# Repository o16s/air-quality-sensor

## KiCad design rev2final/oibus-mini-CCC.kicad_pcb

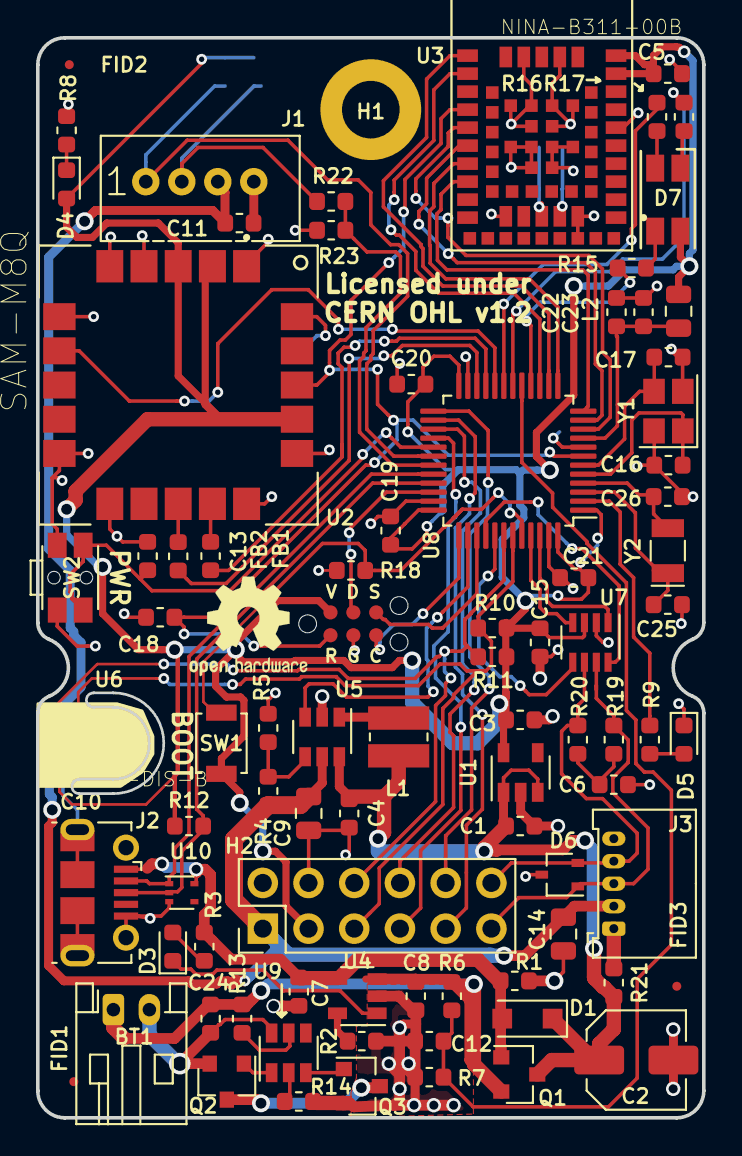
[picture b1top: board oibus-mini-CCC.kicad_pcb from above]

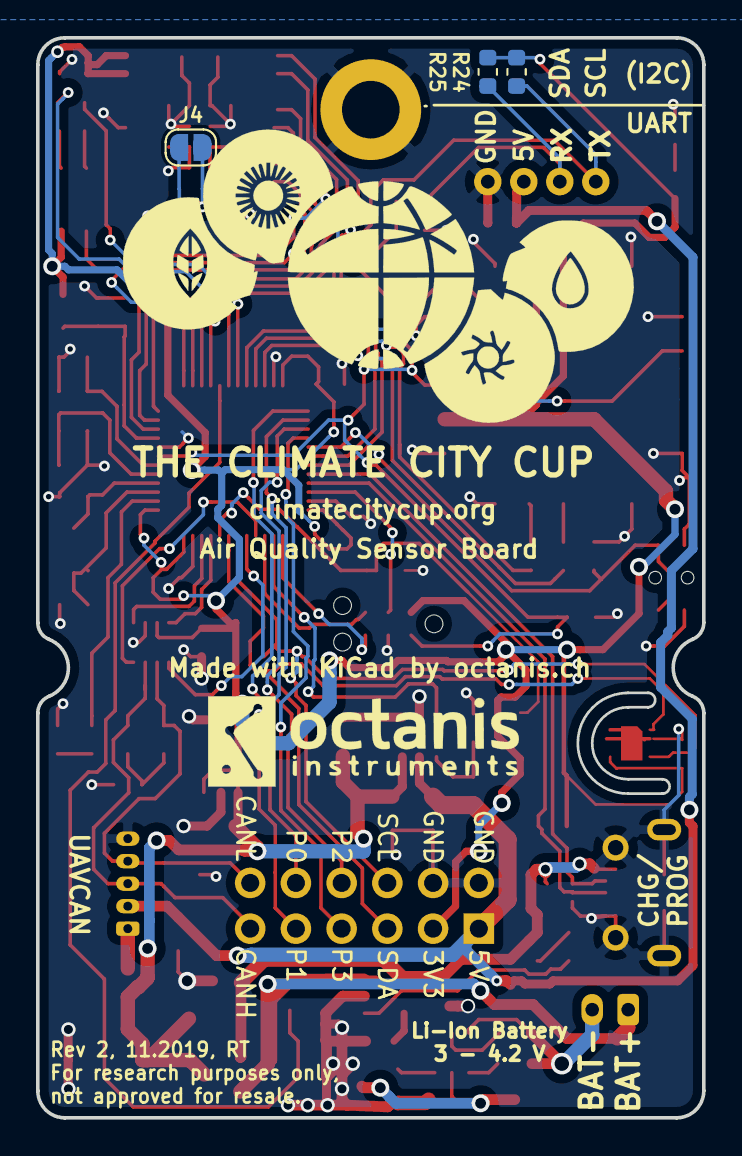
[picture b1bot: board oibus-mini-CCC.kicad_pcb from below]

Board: 2 copper layers, 37.0 x 60.0 mm, 90 parts (4 on the bottom side), 71 nets.

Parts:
B1: OI_Logo; octanis_instruments_logo
BT1: Battery_Cell; JST_PH_S2B-PH-K_1x02_P2.00mm_Horizontal
C1, C3, C22, C24: 1u; C_0603_1608Metric
C2: 47u 16V; C_Elec_5x5.4
C4, C7, C8: 4u7; C_0603_1608Metric
C5, C6, C10, C11, C13, C15, C18, C19, C20, C21: 100n; C_0603_1608Metric
C9, C14: 10u; C_0805_2012Metric
C12, C23: 10n; C_0603_1608Metric
C16, C17: 12p; C_0603_1608Metric
C25, C26: 10p; C_0603_1608Metric
D1: MBR120; D_SOD-123F
D3: LED_red; LED_0603_1608Metric
D4: LED_green; LED_0603_1608Metric
D5: LED_blue_side; LED_0603_1608Metric
D6: DNP; SOT-323_SC-70
D7: LED_RGBA; LED_RGB_1210
FB1, FB2: Ferrite_Bead; L_0603_1608Metric
FID1, FID2, FID3: Fiducial; Fiducial_0.5mm_Mask1mm
H1: MountingHole_Pad; MountingHole_3.2mm_M3_DIN965_Pad
H2: DNP; OIBUS12_connector
J1: Conn_01x04_Female; Grove_1x04
J2: USB_B_Micro; USB_Micro-B_Molex-105017-0001
J3: DNP; Molex_PicoBlade_53048-0510_1x05_P1.25mm_Horizontal
J4: Conn_01x02_Female; SolderJumper-2_P1.3mm_Open_RoundedPad1.0x1.5mm
L1: 4u7; L_Wuerth_MAPI-3010
L2: 10uH; L_0805_2012Metric
P1: TC2030-MCP; TC2030-MCP-NL
Q1: DMG3415U-7; SOT-23
Q2, Q3: NMOS; SOT-23
R1, R5, R6: 309k; R_0603_1608Metric
R2: 5.1k; R_0603_1608Metric
R3, R14, R15, R16: 1.2k; R_0603_1608Metric
R4, R7: 976k; R_0603_1608Metric
R8, R19, R20, R21, R23, R24, R25: DNP; R_0603_1608Metric
R9, R13: 430R; R_0603_1608Metric
R10, R11, R12, R18: 4.7k; R_0603_1608Metric
R17: 2.7k; R_0603_1608Metric
R22: 0R; R_0603_1608Metric
SW1: SW_Push; SW_SPST_B3U-1000P
SW2: SW_Push; SW_SPST_EVQP7C
U1: AP2112K-3.3; SOT-23-5
U2: SAM-M8Q; XCVR_SAM-M8Q
U3: NINA-B311-00B; XCVR_NINA-B312-00B
U4: MCP73831-2-OT; SOT-23-5
U5: MCP1624T; SOT-23-6
U6: SHT31-DIS-B; SON50P250X250X100-9N
U7: DNP; SOT-23-8
U8: STM32F303CCTx; LQFP-48_7x7mm_P0.5mm
U9: DW01C-G; SOT-23-6
U10: TPD3E001DRLR; SOT-553
Y1: 16M; Crystal_SMD_SeikoEpson_FA238-4Pin_3.2x2.5mm
Y2: 32kHz; Crystal_SMD_MicroCrystal_CC7V-T1A-2Pin_3.2x1.5mm

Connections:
+3V3: C3.2, C5.2, C10.2, C15.2, C19.2, C20.2, C21.2, D4.2, D7.4, H2.3, L2.1, P1.2, R10.1, R11.1, R12.1, R24.1, R25.1, SW1.2, U1.5, U2.2, U2.3, U2.17, U3.9, U3.10, U6.5, U7.3, U8.1, U8.24, U8.36, U8.48
+5V: C9.2, C11.2, C14.2, H2.1, J1.3, J3.2, R4.1, U5.5
+BATT: BT1.1, C8.2, C24.2, Q1.2, R6.1, R13.1, U4.3
/5V_EN: U5.3, U8.38
/BAT_MEAS: C12.2, R6.2, R7.1, U8.17
/BLUE: R15.1, U8.16
/BOOT: R18.1, SW1.1, U8.44
/CAN_H: D6.1, H2.11, J3.3, R19.1, U7.7
/CAN_L: D6.2, H2.12, J3.4, R20.2, U7.6
/CAN_LED: R9.1, U8.2
/CAN_RX: U7.4, U8.45
/CAN_SHDN: U7.5, U8.41
/CAN_SILENT: U7.8, U8.40
/CAN_TX: U7.1, U8.46
/GPS_TIME: U2.7, U8.20
/GREEN: R16.1, U8.19
/RED: R17.1, U8.18
/SCL: H2.6, R11.2, U6.4, U8.42
/SDA: H2.5, R10.2, U6.1, U8.43
/SPI_MISO: H2.8, U8.27
/SPI_MOSI: H2.7, U8.28
/SPI_SCK: H2.9, U8.26
/SPS_TX_EXT: J1.2, R22.1, R25.2
/SWDCLK: P1.5, U8.37
/SWDIO: P1.4, U8.34
/SWDSWO: P1.6, U8.39
/USB_DM: J2.2, U8.32, U10.1
/USB_DP: J2.3, R12.2, U8.33, U10.2
/VIN: C1.2, C2.1, C4.2, D1.1, L1.1, Q1.3, R21.2, U1.1, U1.3, U5.6
/on_off: C13.1, SW2.1, U8.29
/~RESET: C18.1, P1.1, U2.18, U3.19, U8.7
/~SPI_ADS_CS: H2.10, U8.25
GND: C1.1, C2.2, C3.1, C4.1, C5.1, C6.1, C7.2, C8.1, C9.1, C10.1, C11.1, C12.1, C13.2, C14.1, C15.1, C16.2, C17.1, C18.2, C19.1, C20.1, C21.1, C22.1, C23.1, C25.2, C26.1, D5.1, D6.3, H1.1, H2.2, H2.4, J1.4, J2.5, J2.6, J3.5, P1.3, Q3.2, R1.2, R2.2, R5.2, R7.2, R8.2, R14.2, R18.2, R23.2, SW2.2, U1.2, U2.1, U2.4, U2.5, U2.6, U2.10, U2.11, U2.15, U2.16, U2.20, U3.6, U3.12, U3.14, U3.26, U3.30, U3.53, U3.EGP1, U3.EGP2, U3.EGP3, U3.EGP4, U3.EGP5, U3.EGP6, U3.EGP7, U3.EGP8, U3.EGP9, U3.EGP10, U3.EGP11, U3.EGP12, U4.2, U5.2, U6.2, U6.7, U6.8, U6.9, U7.2, U8.8, U8.23, U8.35, U8.47, U10.3, Y1.2, Y1.4
GPS_RX: FB1.1, U8.21
GPS_TX: FB2.1, U8.22
NINA_CTS: U3.21, U8.11
NINA_DSR: U3.17, U8.15
NINA_DTR: U3.16, U8.14
NINA_RTS: U3.20, U8.10
NINA_RX: U3.23, U8.12
NINA_TX: U3.22, U8.13
unnamed: BT1.2, C24.1, Q2.2, U9.6
unnamed: C6.2, R19.2, R20.1
unnamed: C16.1, U8.5, Y1.1
unnamed: C17.2, U8.6, Y1.3
unnamed: C22.2, C23.2, L2.2, U8.9
unnamed: C25.1, U8.3, Y2.1
unnamed: C26.2, U8.4, Y2.2
unnamed: D3.1, U4.1
unnamed: D3.2, R3.2
unnamed: D4.1, R8.1
unnamed: D5.2, R9.2
unnamed: D7.1, R17.2
unnamed: D7.2, R16.2
unnamed: D7.3, R15.2
unnamed: FB1.2, U2.14
unnamed: FB2.2, U2.13
unnamed: J3.1, R21.1
unnamed: J4.1, U3.29
unnamed: J4.2, U3.28
unnamed: L1.2, U5.1
unnamed: Q2.1, U9.1
unnamed: Q2.3, Q3.3
unnamed: Q3.1, U9.3
unnamed: R2.1, U4.5
unnamed: R4.2, R5.1, U5.4
unnamed: R13.2, U9.5
unnamed: R14.1, U9.2
SPS_RX: J1.1, R24.2, U8.30
SPS_TX: R22.2, R23.1, U8.31
VBUS: C7.1, D1.2, J2.1, Q1.1, R1.1, R3.1, U4.4, U10.5

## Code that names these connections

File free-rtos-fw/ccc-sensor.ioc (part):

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Mcu.Name=STM32F303C(B-C)Tx
Mcu.Package=LQFP48
Mcu.UserName=STM32F303CCTx
PA0.Mode=CTS_RTS
PA0.Signal=USART2_CTS
PA1.Mode=CTS_RTS
PA1.Signal=USART2_RTS
PA10.Mode=Asynchronous
PA10.Signal=USART1_RX
PA11.Mode=Device
PA11.Signal=USB_DM
PA12.Mode=Device
PA12.Signal=USB_DP
PA13.Mode=Serial_Wire
PA13.Signal=SYS_JTMS-SWDIO
PA14.Mode=Serial_Wire
PA14.Signal=SYS_JTCK-SWCLK
PA15.GPIOParameters=PinState,GPIO_Label
PA15.GPIO_Label=LDO_5V_EN
PA15.PinState=GPIO_PIN_SET
PA15.Signal=GPIO_Output
PA2.Mode=Asynchronous
PA2.Signal=USART2_TX
PA3.Mode=Asynchronous
PA3.Signal=USART2_RX
PA4.GPIOParameters=GPIO_Label
PA4.GPIO_Label=NINA_DTR
PA4.Signal=GPIO_Input
PA5.GPIOParameters=GPIO_Label
PA5.GPIO_Label=NINA_DSR
PA5.Signal=GPIO_Output
PA7.Mode=IN4-Single-Ended
PA7.Signal=ADC2_IN4
PA9.Mode=Asynchronous
PA9.Signal=USART1_TX
PB0.GPIOParameters=GPIO_Label
PB0.GPIO_Label=CAN_SILENT
PB0.Signal=GPIO_Output
PB1.GPIOParameters=GPIO_Label
PB1.GPIO_Label=CAN_SHDN
PB1.Signal=GPIO_Output
PB10.Mode=Asynchronous
PB10.Signal=USART3_TX
PB11.Mode=Asynchronous
PB11.Signal=USART3_RX
PB12.GPIOParameters=GPIO_Label
PB12.GPIO_Label=CS
PB12.Signal=GPIO_Output
PB13.Mode=Full_Duplex_Master
PB13.Signal=SPI2_SCK
PB14.Mode=Full_Duplex_Master
PB14.Signal=SPI2_MISO
PB15.Mode=Full_Duplex_Master
PB15.Signal=SPI2_MOSI
PB2.GPIOParameters=GPIO_Label
PB2.GPIO_Label=GPS_TIME
PB2.Signal=GPIO_Input
PB3.Signal=SYS_JTDO-TRACESWO
PB5.GPIOParameters=GPIO_Label
PB5.GPIO_Label=SHT_ALERT
PB5.Signal=GPIO_Input
PB6.Mode=I2C
PB6.Signal=I2C1_SCL
PB7.Mode=I2C
PB7.Signal=I2C1_SDA
PB8.Mode=Master
PB8.Signal=CAN_RX
PB9.Mode=Master
PB9.Signal=CAN_TX
PC13.GPIOParameters=GPIO_Label
PC13.GPIO_Label=CAN_LED
PC13.Signal=GPIO_Output
PC14-OSC32_IN.Mode=LSE-External-Oscillator
PC14-OSC32_IN.Signal=RCC_OSC32_IN
PC15-OSC32_OUT.Mode=LSE-External-Oscillator
PC15-OSC32_OUT.Signal=RCC_OSC32_OUT
PF0-OSC_IN.Mode=HSE-External-Oscillator
PF0-OSC_IN.Signal=RCC_OSC_IN
PF1-OSC_OUT.Mode=HSE-External-Oscillator
PF1-OSC_OUT.Signal=RCC_OSC_OUT
RCC.HSEPLLFreq_Value=16000000
RCC.HSE_VALUE=16000000
RCC.SYSCLKFreq_VALUE=48000000
RCC.SYSCLKSourceVirtual=RCC_SYSCLKSOURCE_PLLCLK
board=custom

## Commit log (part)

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2019-10-10 created PCB files with all required sensors in schematics, including their footprints
2019-10-18 defined power budget and DC-DC converters components; added to schematics incl. footprints
2019-10-24 added battery protection circuit to allow connecting unprotected Li-Ion cells
2019-10-24 finished all pin assignments. pushed to layout
2019-10-25 Add LICENSE
2019-10-29 grove connector and boot pin correction. added Licence file
2019-10-29 finished component placement
2019-10-29 routing halfway done
2019-10-30 finished routing, DRC clear
2019-10-30 switched UART ports for GPS and SPS, in order to make Grove connector I2C compatible
2019-10-30 Corrected Silkscreen, added CCC logo, OSH logo, License and revision and other labels
2019-10-31 performed some last fixes. Ready to review
2019-10-31 moved the grove connector inside
2019-10-31 corrected the boot pin voltage level
2019-11-13 changed part value where necessary, added MPN where needed, created BOM, created bare code
2019-11-15 created Rev2 PCB based on tests of Rev1
2019-11-16 configured USB and UART ports
2019-11-16 removed old project folder
2019-11-16 adding devcontainer conf
2019-11-16 adding blink, removing old fw folders
2019-11-16 adding measurement task and sps30 drivers
2019-11-16 added NINA basic source code. manufacturer request AT command tested successfully
2019-11-16 adding measurement to user code section
2019-11-16 adding measurement header to user includs
2019-11-16 completed NINA setup
2019-11-16 added USART3 interrupt
2019-11-16 adding sht31 driver
2019-11-16 moving uart rx interrupt callback
2019-11-17 adding UART rx and interrupt handling without HAL, tested and working with sam m8q
2019-11-17 can now update characteristics parametrically
2019-11-17 structured command tx and response rx handling
2019-11-17 padding byte value with leading zero. added LED indication for sent data
2019-11-17 sending out temperature via bluetooth
2019-11-17 adding hardfault handling, adding gps task, fixing sps30 driver
2019-11-17 fixing conflict
2019-11-17 can now parametrically add new characteristics. all added characteristics get updated regularly
2019-11-17 increasing gps task priority or it will not run, increasing sps30 priority or it will produce UART errors, adding CDC print out
2019-11-18 adding example case
2019-11-18 characteristics can now parametrically be added to specific services
2019-11-18 sending true temp, humidity, gps, PM2.5 values
2019-11-18 handling disconnects and reconnects correctly
2019-11-19 adding DS Store to gitignore
2019-11-20 updating case example
2019-11-22 added cut-out for SHT sensor, rotated battery connector, added on-off button
2019-11-23 finished all layout changes for REV2. todo: silkscreen labels
2019-11-24 finished silkscreen V2, generated GERBER files
2019-11-24 Added flashLogger driver
2019-11-24 Linker comment and overwrite protection
2019-11-25 updating cover glass files
2019-11-26 fixing sprintf overflow
2019-11-26 adding emulated FAT fs, tested working
2019-11-27 generated gerber V2
2019-11-27 added battery ADC measurement
2019-11-27 tested battery voltage measurement readings, seems OK
2019-11-27 corrected battery scaling factor for Pei-Chen's board
2019-11-28 adding logging module, fixing FL_Format overflow, adding dynamic row reading to text file
2019-11-28 increased heap size again to activate comm task. battery percentage is displayed correctly
2019-11-28 adding working mini FAT FS code
2019-11-28 increasing size of FAT12 and file
2019-11-28 setting measurement interval to 300s
2019-11-28 enabling sps
2019-11-29 adding webapp
2019-11-30 changing to high contrast map tiles
2019-11-30 fixing pm color ranges
2019-12-01 adding FAT12 documentation
2019-12-01 migrating software away
2019-12-03 updated schematics with tested values
2019-12-03 re-routed RGB LED in final Version 2
2019-12-12 generated final rev2 assembly files ready for PCBA
2020-01-03 started generating panels
2020-03-06 updated LCSC part numbers for all components
2020-03-06 Generated final Manufacturing BOM as ordered
2020-03-31 restructured files and folders
2020-04-03 added final BOM with proven parts values; de-cluttered repository; generated HTML BOM
2025-11-03 updating dashboard
2025-11-04 updating names
2025-11-04 add mock mode
2025-11-05 updated web app to spec
2025-11-05 ading time sync
2025-11-06 updating interface
2025-11-06 adding acquire
2026-01-25 feat: add Electron desktop app with CI builds
2026-01-25 feat: add GitHub Actions workflow for Electron builds
2026-01-25 feat: switch Windows installer from Squirrel to WiX MSI
2026-01-25 fix: add Squirrel event handling for Windows Start Menu shortcuts
2026-01-30 adding experimental features, settings, help, language

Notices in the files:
rev2final/oibus-mini-CCC.kicad_pcb:
Licensed under
CERN OHL v1.2
